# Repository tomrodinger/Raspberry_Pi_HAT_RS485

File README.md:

# Raspberry_Pi_HAT_RS485
This is a Raspberry Pi HAT for RS485 communication with external devices and it should fit into any Raspberry Pi like Zero/Zero2W/3/4

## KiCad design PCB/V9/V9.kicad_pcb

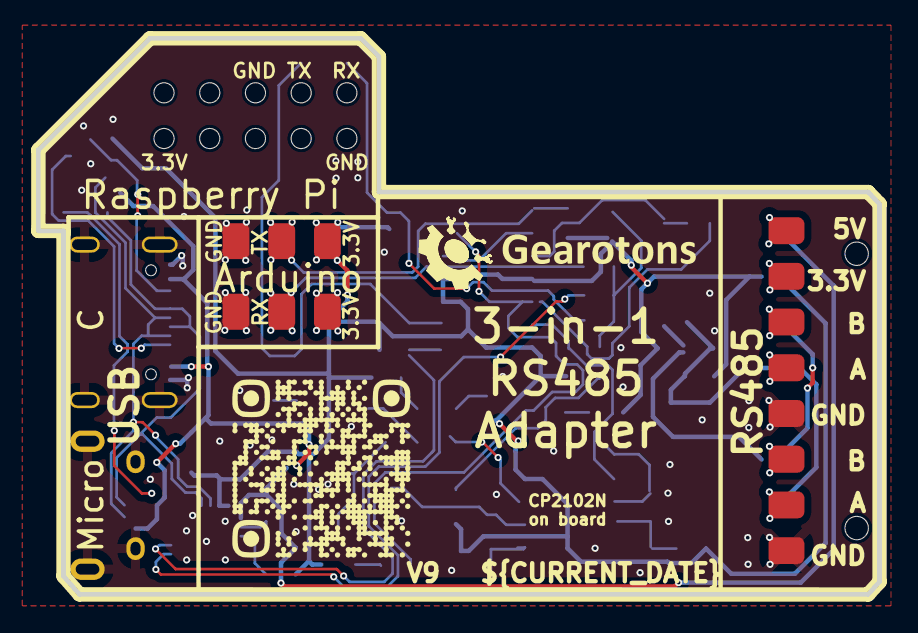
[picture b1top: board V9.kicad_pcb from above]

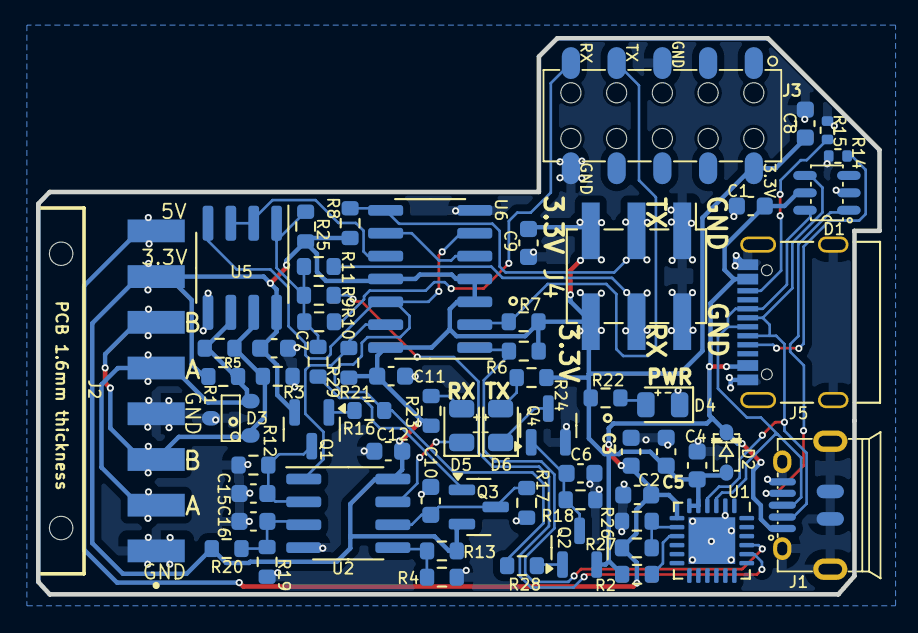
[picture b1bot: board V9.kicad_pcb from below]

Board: 2 copper layers, 46.7 x 30.9 mm, 76 parts (62 on the bottom side), 35 nets.

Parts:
C1: 22pF/50V; C_0603_1608Metric
C2, C4, C7, C8, C9, C11, C12, C16: 100nF/50V; C_0603_1608Metric
C3, C5: 10uF/10V; C_0603_1608Metric
C6, C10: 10nF; C_0603_1608Metric
C15: 1nF; C_0603_1608Metric
D1: TVS_5V; SOT23-6L
D2: 1N5819WS; SOD323
D3: SM712; SOT23-3
D4: yellow; LED_0805_2012Metric
D5: green; LED_0805_2012Metric
D6: red; LED_0805_2012Metric
J1: USB-Micro; usb-MicroXNJ
J2: TSM-108-01-T-SH-A-P-TR; SAMTEC_TSM-108-01-T-SH-A-P-TR_hole1.5mm
J3: Raspberry-Pi_2x5-Pin_Header; con-WR-PHD-61031021821
J4: Conn_02x03_Odd_Even; PinHeader_2x03_P2.54mm_Vertical_SMD
J5: USB_C_Receptacle; USB_C_Receptacle_Palconn_UTC16-G
Q1, Q2, Q3: BSS84AK,215; SOT-23
Q4: Q_NMOS_GSD; SOT-23
R1, R3: 560R; R_0603_1608Metric
R2, R21, R28, R29: 4.7k; R_0603_1608Metric
R4, R13, R20, R26: 20k; R_0603_1608Metric
R5: 220R; R_0603_1608Metric
R6, R7, R8, R16, R19, R22, R25, R27: 10k; R_0603_1608Metric
R9, R10, R11, R12: 1k; R_0603_1608Metric
R14, R15: 5.1k; R_0402_1005Metric
R17, R18: 10M; R_0603_1608Metric
R23, R24: 75R; R_0603_1608Metric
TP1, TP2, TP3, TP4, TP5, TP6, TP7, TP8, TP9, TP10, TP11, TP12, TP13, TP14: TestPoint; testpoint_no_border
U1: CP2102N-A02-GQFN24R; QFN-24-1EP_4x4mm_P0.5mm_EP2.6x2.6mm
U2: LM393DR2G; SOIC-8_3.9x4.9mm_P1.27mm
U5: SP3485EN; SOIC-8_3.9x4.9mm_P1.27mm
U6: CD4023BM/TR; SOIC-14_3.9x8.7mm_P1.27mm

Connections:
+3.3V: C4.1, C5.1, C7.2, C8.1, C9.2, C11.2, C12.2, D2.1 (A), J2.7, J3.2 (3.3V), J4.5, J4.6, Q1.2 (S), Q2.2 (S), Q3.2 (S), R1.1, R2.2, R6.1, R7.1, R8.1, R13.2, R20.1, R21.2, R22.1, R23.1, R24.1, R25.2, TP1.1, TP2.1, TP13.1, U1.5 (VIO), U1.6 (VDD), U2.8 (V+), U5.8 (VCC), U6.3, U6.4, U6.11, U6.14 (VDD)
+5V: C1.1, C2.1, C3.1, D1.5 (VDD), D2.2 (K), J1.1 (VCC), J2.8, J5.A4 (VBUS), J5.A9 (VBUS), J5.B4 (VBUS), J5.B9 (VBUS), R27.2, TP14.1, U1.7 (VREGIN)
/index/schTop/RS485A: D3.2 (cathode), J2.2, J2.5, R1.2, R5.1, TP8.1, TP11.1, U5.6 (A)
/index/schTop/RS485B: D3.1 (Anode), J2.3, J2.6, R3.2, R5.2, TP9.1, TP12.1, U5.7 (B)
/index/schTop/RXD: R9.2, R10.2, R11.2, R25.1, R29.2, U5.1 (RO)
/index/schTop/RXDA: J4.4, R11.1, TP6.1
/index/schTop/RXDR: J3.9 (GPIO_15(RXD0)), R10.1
/index/schTop/RXDU: R9.1, U1.20 (RXD)
/index/schTop/TXD: R16.1, R28.2, U5.4 (DI), U6.6, U6.12
/index/schTop/TXDA: J4.3, R8.2, TP5.1, U6.8
/index/schTop/TXDR: J3.7 (GPIO_14(TXD0)), R7.2, U6.2
/index/schTop/TXDU: R6.2, U1.21 (TXD), U6.1
/index/schTop/TXEN: U5.2 (~RE), U5.3 (DE), U6.10
/index/schTop/USB_D+: D1.6 (IO4), J1.3 (D+), J5.A6 (D+), J5.B6 (D+), U1.3 (D+)
/index/schTop/USB_D-: D1.4 (IO3), J1.2 (D-), J5.A7 (D-), J5.B7 (D-), U1.4 (D-)
/index/schTop/VBUS_div: R26.2, R27.1, U1.8 (VBUS)
/index/schTop/~RST: R2.1, U1.9 (~RST)
GND: C1.2, C2.2, C3.2, C4.2, C5.2, C6.1, C7.1, C8.2, C9.1, C10.1, C11.1, C12.1, C15.1, C16.1, D1.2 (GND), D3.3 (AK), D4.1 (K), J1.5 (GND), J1.6 (CH), J2.1, J2.4, J3.5 (GND), J3.10 (GND), J4.1, J4.2, J5.A1 (GND), J5.A12 (GND), J5.B1 (GND), J5.B12 (GND), J5.S1 (SHIELD), Q4.2 (S), R3.1, R4.1, R12.1, R14.2, R15.2, R17.1, R18.1, R19.1, R26.1, TP3.1, TP4.1, TP7.1, TP10.1, U1.2 (GND), U1.25 (GND), U2.4 (V-), U5.5 (GND), U6.7 (VSS)
unnamed: D1.1 (IO1), J1.4 (ID)
unnamed: D4.2 (A), R22.2
unnamed: D5.2 (A), R23.2
unnamed: D6.2 (A), R24.2
unnamed: D6.1 (K), Q4.3 (D)
unnamed: J5.A5 (CC1), R14.1
unnamed: J5.B5 (CC2), R15.1
unnamed: C15.2, Q1.3 (D), R12.2, U2.2 (-)
unnamed: Q1.1 (G), R16.2
unnamed: C6.2, Q2.3 (D), Q4.1 (G), R18.2
unnamed: Q2.1 (G), R28.1
unnamed: C10.2, Q3.3 (D), R17.2, U2.6 (-)
unnamed: Q3.1 (G), R29.1
unnamed: R21.1, U2.1, U6.13
unnamed: C16.2, R19.2, R20.2, U2.3 (+)
unnamed: R4.2, R13.1, U2.5 (+)
unnamed: U6.5, U6.9

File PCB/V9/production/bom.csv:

Designator,Footprint,Quantity,Value,LCSC Part #
C1,0603,1,22pF/50V,C1653
"C10, C6",0603,2,10nF,C57112
"C11, C12, C16, C2, C4, C7, C8, C9",0603,8,100nF/50V,C14663
C15,0603,1,1nF,C1588
"C3, C5",0603,2,10uF/10V,C19702
D1,SOT23-6L,1,TVS_5V,C558417
D2,SOD323,1,1N5819WS,C191023
D3,SOT23-3,1,SM712,C293966
D4,0805,1,yellow,C2296
D5,0805,1,green,C2297
D6,0805,1,red,C84256
J1,usb-MicroXNJ,1,USB-Micro,C404969
J2,SAMTEC_TSM-108-01-T-SH-A-P-TR_hole1.5mm,1,TSM-108-01-T-SH-A-P-TR,
J3,con-WR-PHD-61031021821,1,Raspberry-Pi_2x5-Pin_Header,C261072
J4,PinHeader_2x03_P2.54mm_Vertical_SMD,1,Conn_02x03_Odd_Even,C192301
J5,USB_C_Receptacle_Palconn_UTC16-G,1,USB_C_Receptacle,C2765186
"Q1, Q2, Q3",SOT-23,3,"BSS84AK,215",C127273
Q4,SOT-23,1,Q_NMOS_GSD, C8545
"R1, R3",0603,2,560R,C23204
"R10, R11, R12, R9",0603,4,1k,C21190
"R13, R20, R26, R4",0603,4,20k,C4184
"R14, R15",0402,2,5.1k,C25905
"R16, R19, R25, R27, R6, R7, R8",0603,7,10k,C25804
"R17, R18",0603,2,10M,C7250
"R2, R21, R28, R29",0603,4,4.7k,C23162
R22,0603,1,10k, C25804
"R23, R24",0603,2,75R,C4275
R5,0603,1,220R,C22962
"TP1, TP10, TP11, TP12, TP13, TP14, TP2, TP3, TP4, TP5, TP6, TP7, TP8, TP9",testpoint_no_border,14,TestPoint,
U1,QFN-24-1EP_4x4mm_P0.5mm_EP2.6x2.6mm,1,CP2102N-A02-GQFN24R,C969151
U2,SOIC-8_3.9x4.9mm_P1.27mm,1,LM393DR2G,C7955
U5,SOIC-8_3.9x4.9mm_P1.27mm,1,SP3485EN,C8963
U6,SOIC-14_3.9x8.7mm_P1.27mm,1,CD4023BM/TR,C910853

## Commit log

2023-06-01 Organising folders. Adding schematic Adding older V3 PCB Adding PRODUCT_DATA.yaml
2023-06-11 Cleaning up some PCB files that should not be in the root folder.
2023-06-19 Adding V5 of the PCB. Here we changed the logic for enabling the DE (drive enable) line on the RS480 tranceiver because previous version had flawed logic and did not work 100% correctly.
2025-10-18 Adding PCB files for V9, 1.1, and 1.2 Modifying the PRODUCT_DATA.yaml file to include the new versions of the product Adding more up to date pictures Adding a .gitignore Adding a test program that se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
2025-10-18 Attempting to fix a link to the schematic for V9, 1.1, 1.2
2025-10-18 Another attempt to fix the link to the schematics
2025-11-18 Updating the PCB to remove the test points from the BOM and also to substitute the raspberry pi header part number because the previous one was out of stock in JLCPCB.
2025-11-18 Adding the first version of the datasheet along with the program that generates it.
2025-11-19 Updating the link to the datasheet so that it is the correct one.
